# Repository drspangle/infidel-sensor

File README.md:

# Inline Filament Diameter Estimator, Lowcost (InFiDEL)

<p xmlns:dct="http://purl.org/dc/terms/" xmlns:vcard="http://www.w3.org/2001/vcard-rdf/3.0#">
  
  Originally created by Thomas Sanladerer
</p>

*A cheap, yet precise filament diameter sensor, intended to compensate for filament diameter deviations in real-time.*

The InFiDEL is a cheap (< $5) filament diameter sensor intended for use with FDM 3d printers.
The sensor can be calibrated to provide surprisingly precise filament diameter readings in real-time. 
The main idea is to use the sensor to correct for filament diameter deviations while printing.

Based on this proof-of-concept: https://www.youmagine.com/designs/filament-diameter-sensor

Detailed documention for InFiDEL: https://infidel-sensor.readthedocs.io/

## Assembly and Setup

### Calibration
- Flash board with calibration.ino
- Connect a host via I2C (see provided host-example.ino)
- Insert each calibration drill bit shafts and replace the lookup table entries in driver.ino with your own measurements
  * Measure the actual diameter of the shafts and fill second column
  * Use the host's output *1000 to fill first column
- Finally, flash driver.ino with your values filled out
- Hub should now output exact diameter values

#### Note:
Analog output is currently not enabled in driver.ino (I2C and FAULT pin only)

## BOM

### Printed Parts
1 Block
1 Lever

#### Note:
Parts should preferably be printed in PETG, ABS or ASA as PLA may creep significantly over time.

### Electronics
There are two board variants included in this repository, either can be used to assemble the InFiDEL. 
PCBs and electronic components can be easily ordered via the [Kitspace project page](https://kitspace.org/boards/github.com/drspangle/infidel-sensor/) as it can auto-fill carts and get pricing on PCBs and electronic components from common suppliers.

Choose one:
- SMT control board (which is populated; Gerber files and component specifications are included) 
- THT control board

Also required:

- Suitable programmer for ATTiny85 (eg USBtinyISP)
- 1 SS495A linear hall effect sensor (or comparable)

### Fasteners
- 2 M3x8 screws (eg ISO 4762 M3x8)
- 1 3x24mm pin (eg DIN 7 3x24mm, for mating lever to the block)
- 1 3x16mm pin (eg DIN 7 3x16mm, for roller bearing in lever)
- 1 3x18mm pin (eg DIN 7 3x18mm, for idler bearing in block)
- 6 M3 threaded inserts
- 1 M6x5 or M6x8 grub screw (eg ISO 4026 M6x5, for pre loading spring) 

Pins may be replaced with screws or grubscrews, which may result in decreased precision.

### Other Hardware
- 1 6x2mm magnet (eg N35)
- 4 623 bearings (preferably 623-2Z / 623-ZZ)
- 1 Ballpoint pen spring (or other soft 4mm spring)
- Short length of PTFE tube

### Calibration Accessories
- 1 1.5mm drill bit
- 1 1.7mm or 1.8mm drill bit 
- 1 2mm drill bit
- Calipers for verifying drill bit shaft diameter

Drill bits may be replaced with similar diameters. 
Measured diameter is to be written to firmware lookup table.

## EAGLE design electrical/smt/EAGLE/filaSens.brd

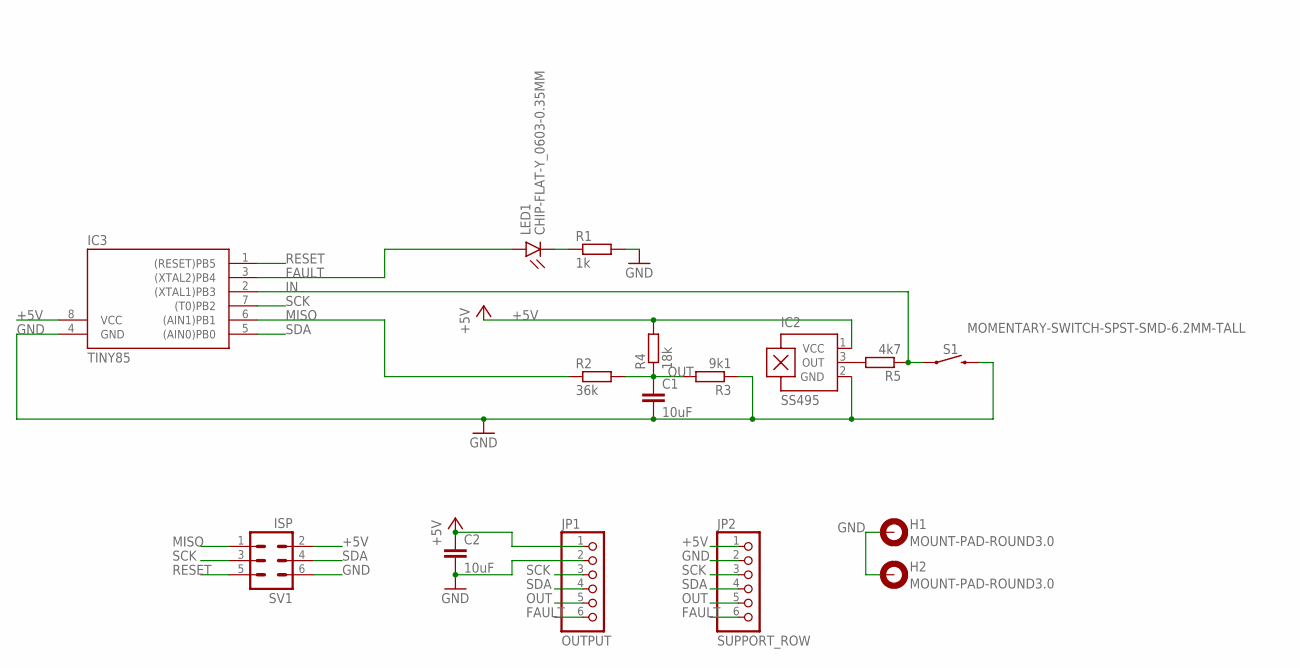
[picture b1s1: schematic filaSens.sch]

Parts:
C1, C2: 10uF; C0402
H1, H2: MOUNT-PAD-ROUND3.0; 3,0-PAD
IC2: SS495; SIP3-UA
IC3: TINY85; SOIC8
JP1: OUTPUT; 1X06
JP2: SUPPORT_ROW; 1X06
LED1: CHIP-FLAT-Y_0603-0.35MM; LEDC1608X35N_FLAT-Y
R1: 1k; R0402
R2: 36k; R0402
R3: 9k1; R0402
R4: 18k; R0402
R5: 4k7; R0402
S1: MOMENTARY-SWITCH-SPST-SMD-6.2MM-TALL; TACTILE_SWITCH_SMD_6.2MM_TALL
SV1: ISP; MA03-2

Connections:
+5V: C2.1, IC2.1 (VCC), IC3.8 (VCC), JP1.1, JP2.1, R4.2, SV1.2
FAULT: IC3.3 ((XTAL2)PB4), JP1.6, JP2.6, LED1.A
GND: C1.2, C2.2, H1.B3,0, H2.B3,0, IC2.2 (GND), IC3.4 (GND), JP1.2, JP2.2, R1.2, R3.1, S1.B2 (2), SV1.6
IN: IC3.2 ((XTAL1)PB3), R5.1, S1.A2 (1)
MISO: IC3.6 ((AIN1)PB1), R2.1, SV1.1
unnamed: IC2.3 (OUT), R5.2
unnamed: LED1.C, R1.1
OUT: C1.1, JP1.5, JP2.5, R2.2, R3.2, R4.1
RESET: IC3.1 ((RESET)PB5), SV1.5
SCK: IC3.7 ((T0)PB2), JP1.3, JP2.3, SV1.3
SDA: IC3.5 ((AIN0)PB0), JP1.4, JP2.4, SV1.4

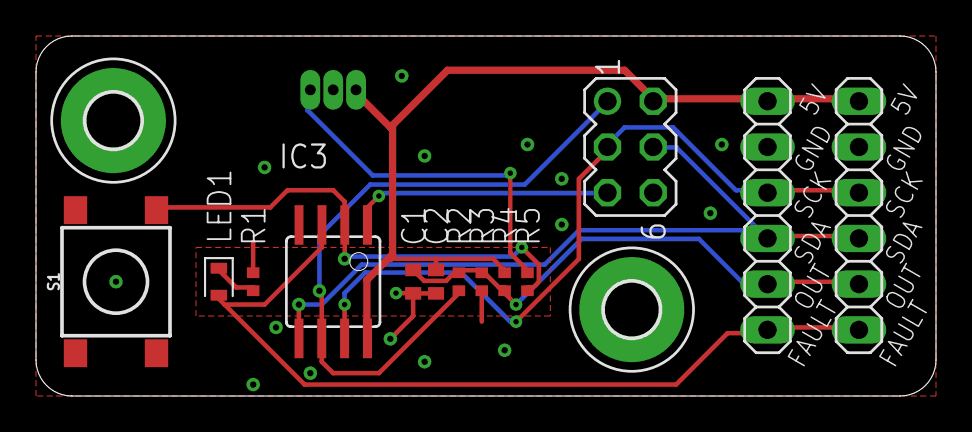
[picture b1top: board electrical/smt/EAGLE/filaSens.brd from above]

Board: 2 copper layers, 50.0 x 20.0 mm, 16 parts (1 on the bottom side), 11 nets.

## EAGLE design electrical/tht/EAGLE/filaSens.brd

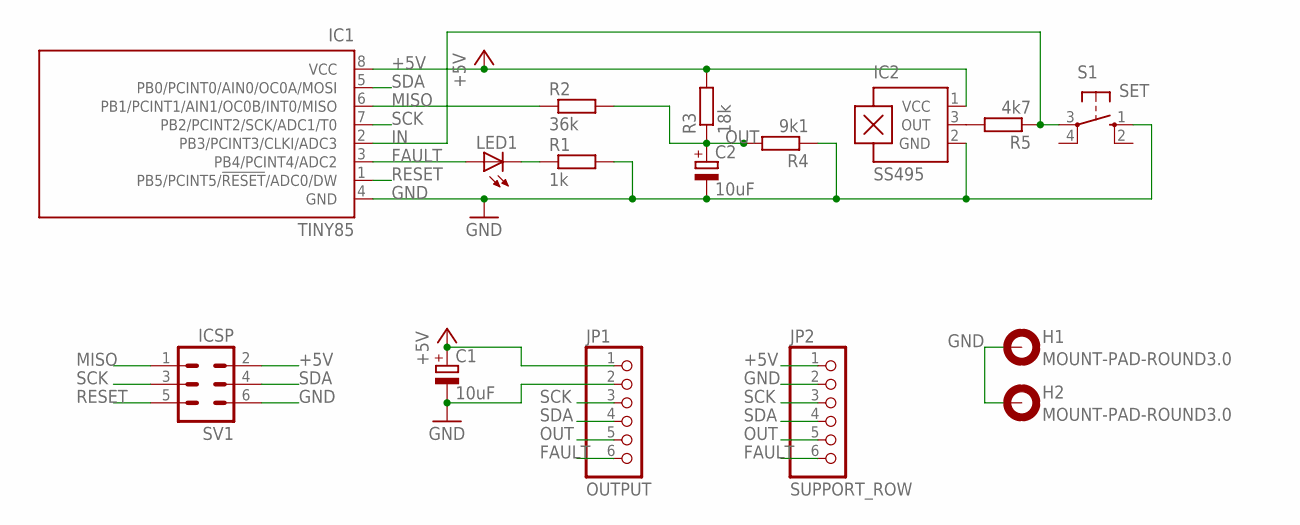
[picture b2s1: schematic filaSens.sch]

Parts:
C1, C2: 10uF; E2,5-5
H1, H2: MOUNT-PAD-ROUND3.0; 3,0-PAD
IC1: TINY85; DIL08
IC2: SS495; SIP3-UA
JP1: OUTPUT; 1X06
JP2: SUPPORT_ROW; 1X06
LED1: TLLG4400; LED3MM
R1: 1k; 0207/10
R2: 36k; 0207/10
R3: 18k; 0207/10
R4: 9k1; 0207/10
R5: 4k7; 0207/10
S1: SET; B3F-10XX
SV1: ICSP; MA03-2

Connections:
+5V: C1.+, IC1.8 (VCC), IC2.1 (VCC), JP1.1, JP2.1, R3.2, SV1.2
FAULT: IC1.3 (PB4/PCINT4/ADC2), JP1.6, JP2.6, LED1.A
GND: C1.-, C2.-, H1.B3,0, H2.B3,0, IC1.4 (GND), IC2.2 (GND), JP1.2, JP2.2, R1.2, R4.1, S1.1 (S), SV1.6
IN: IC1.2 (PB3/PCINT3/CLKI/ADC3), R5.1, S1.3
MISO: IC1.6 (PB1/PCINT1/AIN1/OC0B/INT0/MISO), R2.1, SV1.1
unnamed: IC2.3 (OUT), R5.2
unnamed: LED1.K (C), R1.1
OUT: C2.+, JP1.5, JP2.5, R2.2, R3.1, R4.2
RESET: IC1.1 (PB5/PCINT5/!RESET!/ADC0/DW), SV1.5
SCK: IC1.7 (PB2/PCINT2/SCK/ADC1/T0), JP1.3, JP2.3, SV1.3
SDA: IC1.5 (PB0/PCINT0/AIN0/OC0A/MOSI), JP1.4, JP2.4, SV1.4

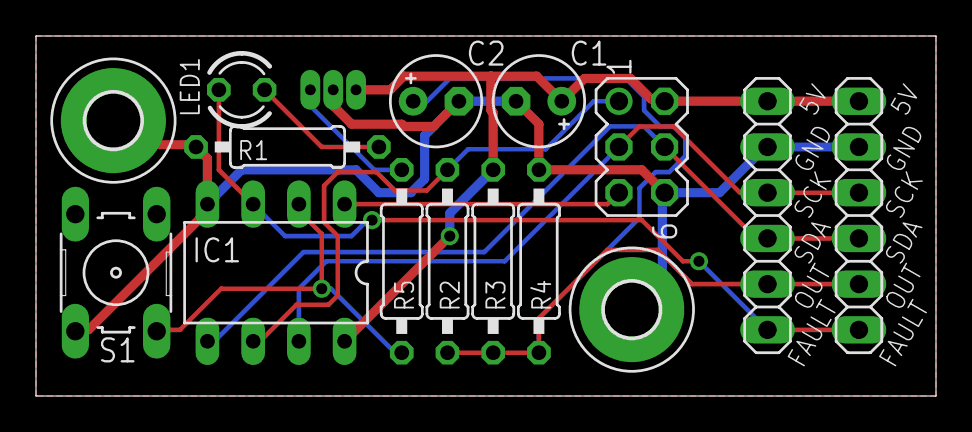
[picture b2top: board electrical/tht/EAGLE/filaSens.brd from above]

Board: 2 copper layers, 50.0 x 20.0 mm, 16 parts (1 on the bottom side), 11 nets.

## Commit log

2021-02-20 Updated README.md
    Improved the formatting of the Electronics section, properly spacing the items.
2021-02-20 Update README.md
    Added basic description of the project, taken from the YouMagine and prusaprinters pages
2021-02-20 Update README.md
    Added CC-0 license to top of README
2021-02-20 Create LICENSE
    Added CC0 license.
2021-02-20 Update README.md
    Removed all the extraneous CC0 text, it's really not helping anyone.
2021-02-20 Update README.md
    Added Tom's name as attribution at the top. Might as well.
2021-02-20 Update README.md
    Added youtube link for assembly instructions
2021-02-20 add schematic png
    Add png file so Eagle isn't necessary to view the schematic.
2021-03-05 Create Infidel_release_ee.ino
    - Firmware for Sensor with Table in EEPROM
    - Set Table Values over I2C
    - Get Diameter oder RAW Value over I2C
    - Read Table over I2C
2021-03-05 Host Version with I2C Table Programm function
    - Read an write the Table
    - read RAV Value
    - Read Diameter
    - Set Table Valuse over Serial Konsole
2021-03-05 Wire Diagramm Host to Sensor
2021-03-05 Update README.md
    - First documentaion
2021-03-05 Update README.md
    Typo
2021-03-06 Rangecontrol for Input ignore Value 3000, fixed
2021-03-06 Add simple XOR Checksum to Check EEPROM content
2021-03-06 Add Command 5, Ongoing read raw Value
    - Start continuously read rae value with Command 5
    - Stop continuously read rae value with repeat sending Command 5
2021-03-06 Check device on I2C Adress on startup
2021-03-06 Typo
2021-03-07 Update Lever.stl
    Update Lever.stl to remove infinitely thin walls and generally improve printability
2021-03-07 Update BOM and CPL so JLCPCB can read it properly
    For some reason when the line for the switch is present in the files the preview of the pick and place locations are incorrect, if you just remove the switch everything seems to work. I do not unders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
2021-03-07 Revert "Update BOM and CPL so JLCPCB can read it properly"
    This reverts commit 6b8723a0ccd6b4eb5a09a49f7a27d93d473241ef.
2021-03-07 Update filaSens_top_bom.csv
    Update so JLCPCB can read it properly
2021-03-07 Update filaSens_top_cpl.csv
    Update so JLCPCB can read it properly
2021-03-07 Update README.md
    Corrected M2 to M3 and added details of grub screw for pre loading the spring.
2021-03-07 Revert "Update Lever.stl"
    This reverts commit 5b47a934cdd4212848215bc6d2364750ca59b7f2.
2021-03-08 Create LeverDB.f3d
    Export the modified lever arm, I have called it LeverDB to distinguish it from the original, and there is a small DB inset into the base of the lever.
2021-03-14 Settings for the attiny and Fuses
2021-03-14 Typo add CR
2021-03-24 create BOM.md and format the csv into it
    I took the BOM from the Gerber files and reformatted them into a Markdown table
2021-03-24 added Mouser as vendor
    Added Mouser with mouser part number and included link to .com site
2021-03-24 Fixed LED Mouser Number and added Sensor and Pins
    Removed the ":" in the LED Mouser part number.
    Added The SS495A Sensor
    Added Pin headers for ISP and I2C
2021-04-10 Typo
    Tabel --> Table
2021-04-16 Change grubscrew M5 to M6
    Addresses #21
2021-04-16 Command "6" for read ADC Meanvalue from Sensor
2021-04-16 Description for Standalnoe Calibration
2021-04-16 Standalone Calibration with Button
    - Standalone Calibration with butten
    - Replace byte to unit8_t, ...
    - Change Delay for 1 Mhz Clock
    - Command I2C_CMD_MEANVAL to send the Meanval over 100 Samples
    - Command 6, to read Meanvalue over 100 Samples with Peak remove for Calibration value
    -If Diameter is smaller then 1,4mm or bigger 2,1mm the Alanogout swap from min to max.
2021-04-17 command "7" to set the DAC
    - Override the DAC Output for Calibrate the DAC Output
2021-04-17 Opion the Calibrate the DAC Out
    By means of commands "7" and "8" the DAC can be set to LOW and HIGH, the output is measured with a multimeter and the values are stored in the EEPROM.
2021-04-17 feat: Adds initial kitspace code to test
2021-04-17 fix: Updates title for comment to description in 1-click-bom.csv
2021-04-17 Startscreen on Terminal update
2021-04-17 Send ack byte when Table Values are set
2021-04-17 Fix EAGLE path in kitspace.yaml
2021-04-17 Add KiCAD Files for SMT Version
2021-04-23 fix capacitor grounds not connected
2021-04-23 change EAGLE files to capture PR #28 and Issue #27
    change EAGLE files to capture PR #28 and Issue #27
    Update GERBER files as well as EAGLE files
2021-04-24 feat: Adds kitspace project link & explanation to readme
    Would resolve issue #30 if merged
2021-04-24 Added missing linebreak
2021-05-15 feat: Adds autogenerated build of sphinx/readthedocs
2021-05-15 feat: Adds initial readme content
2021-05-16 feat: Adds Python .gitignore for docs
2021-05-16 fix: Adjusts .gitignore for just the doctree
2021-05-16 feat: Adds rebuilt files after adjusting the .gitignore
2021-05-29 fix: Adding .nojekyll file to prevent the ignoring of folders beginning with a _
2021-05-29 Adding arbitrary space to try to rebuild github page after adjusting .nojekyll
2021-05-29 Set theme jekyll-theme-cayman
2021-05-29 removing arbitrary white space
2021-05-29 feat: Creates .nojekyll file in docs folder
2021-06-19 Update issue templates
2021-06-19 Moved compiled documentation to correct folder
    Moved source files to their own docs-src folder as well, docs should be compiled separately and moved to the docs folder to ensure that the github-pages URLs are based on the /docs/ root folder, so t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
2021-06-19 moved over the config files from the sources folder
2021-06-20 feat: Adds additional files after rebuilding
2021-06-20 fix: Manually deletes contents of docs/build/html folder
2021-06-20 fix: Manually removes source folder from docs directory
2021-06-20 fix: Removes unnecessary make files from docs folder
2021-06-20 feat: Adds initial link & explanation of how to build the docs
2021-06-20 feat: Adds more context to the documentation section in the readme
2021-06-20 fix: small update to make the readme more readable
2021-06-20 fix: Corrects typo error in readme
2021-06-20 docs: Adds folder structure for firmware to fill in
2021-06-20 feat: Ports current content to firmware.rst
2021-06-20 fix: Corrects bullet point in calibration section of firmware docs
2021-06-20 Updated README
    Added a link to the documentation for InFiDEL
2021-06-26 fix: Updates docs instructions to match latest version
2021-07-01 Fixed cap gnd, made 5v trace larger, re-routed some traces to be cleaner
2021-07-10 added issue forms, gh-pages automation on release
2021-07-10 fixed quotes (' | ")
2021-07-10 added .nojekyll
2021-07-10 issue forms working
2021-07-10 well now they are
2021-07-10 here we go again
2021-07-10 polished issue tempates
2021-07-10 Initial gh-pages commit
2021-07-10 Deploying to gh-pages from @ drspangle/infidel-sensor@38828dd123c71507028826171dc960794db38469 🚀
2021-07-10 Removed local sphinx build instructions
2021-07-10 feat: Updates docs link & instructions (#47)
    * feat: Adds initial link & explanation of how to build the docs
    * feat: Adds more context to the documentation section in the readme
    * fix: small update to make the readme more readable
    * fix: Corrects typo error in readme
    * fix: Updates docs instructions to match latest version
    * Removed local sphinx build instructions
2021-07-11 added firmware.rst
2021-07-11 created test branch
2021-07-11 changed label from 'feature-req' to 'enhancement'
2021-07-13 punctuation changes
2021-08-29 fix: Corrects link to documentation
    Link now points to the readthedocs link https://infidel-sensor.readthedocs.io/, would resolve https://github.com/drspangle/infidel-sensor/issues/60
2021-11-26 Update conf.py
    Removed the code which @leonhma recommended, in order to fix bugs introduced in #61. Should fix #60.

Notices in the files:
README.md:
href="http://creativecommons.org/publicdomain/zero/1.0/">
electrical/smt/EAGLE/filaSens.brd:
Licensed as Public Domain
parts and their libraries:
SparkFun-Switches: Licensing: Creative Commons ShareAlike 4.0 International - https://creativecommons.org/licenses/by-sa/4.0
